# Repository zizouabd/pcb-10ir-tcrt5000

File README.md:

# Module de Capteurs Suiveur de Ligne (10x TCRT5000)

Ce projet contient les fichiers de conception pour un module PCB incurvé conçu pour le suivi de ligne, intégrant 10 capteurs infrarouges TCRT5000.

## Schéma Électrique
Le circuit est composé de 10 capteurs optiques (U1 à U10), chacun accompagné d'une résistance de 220 ohms pour la LED émettrice et d'une résistance de pull-up de 10k ohms pour le phototransistor récepteur[cite: 1]. Les signaux (SIG_S1 à SIG_S10) sont regroupés sur un connecteur central à 12 broches avec l'alimentation (VCC) et la masse (GND).

## Routage du PCB
Le routage a été optimisé sur un circuit imprimé de forme incurvée pour s'adapter à l'avant d'un robot, avec deux trous de montage (H1 et H2).

## Vues 3D

### Face Supérieure (Composants)
La face supérieure accueille l'ensemble des résistances traversantes, le condensateur de découplage, et le connecteur principal J1.

### Face Inférieure (Capteurs)
La face inférieure est dédiée exclusivement aux 10 capteurs infrarouges TCRT5000 orientés vers le sol pour la détection de ligne.

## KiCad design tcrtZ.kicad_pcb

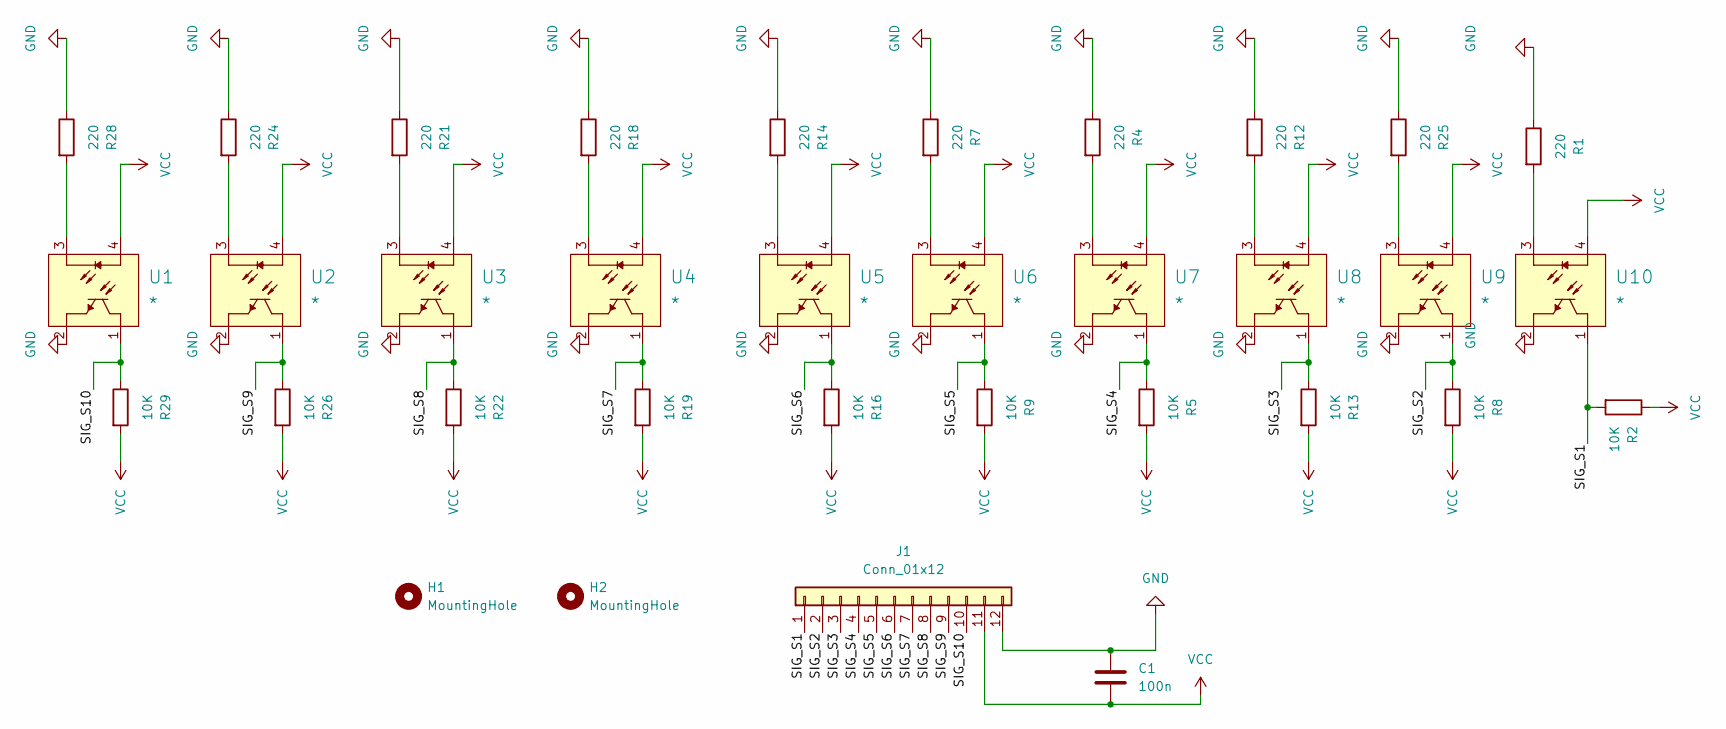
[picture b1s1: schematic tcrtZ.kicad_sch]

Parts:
C1: 100n; C_0805_2012Metric_Pad1.18x1.45mm_HandSolder
H1, H2: MountingHole; MountingHole_3.2mm_M3
J1: Conn_01x12; PinHeader_1x12_P2.54mm_Vertical
R1, R4, R7, R12, R14, R18, R21, R24, R25, R28: 220; R_Axial_DIN0207_L6.3mm_D2.5mm_P10.16mm_Horizontal
R2, R5, R8, R9, R13, R16, R19, R22, R26, R29: 10K; R_Axial_DIN0207_L6.3mm_D2.5mm_P10.16mm_Horizontal
U1, U2, U3, U4, U5, U6, U7, U8, U9, U10: *; Vishay_TCRT5000

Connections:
/SIG_S1: J1.1, R2.2, U10.1 (CO)
/SIG_S2: J1.2, R8.1, U9.1 (CO)
/SIG_S3: J1.3, R13.1, U8.1 (CO)
/SIG_S4: J1.4, R5.1, U7.1 (CO)
/SIG_S5: J1.5, R9.1, U6.1 (CO)
/SIG_S6: J1.6, R16.1, U5.1 (CO)
/SIG_S7: J1.7, R19.1, U4.1 (CO)
/SIG_S8: J1.8, R22.1, U3.1 (CO)
/SIG_S9: J1.9, R26.1, U2.1 (CO)
/SIG_S10: J1.10, R29.1, U1.1 (CO)
GND: C1.1, J1.12, R1.1, R4.1, R7.1, R12.1, R14.1, R18.1, R21.1, R24.1, R25.1, R28.1, U1.2 (E), U2.2 (E), U3.2 (E), U4.2 (E), U5.2 (E), U6.2 (E), U7.2 (E), U8.2 (E), U9.2 (E), U10.2 (E)
unnamed: R28.2, U1.3 (C)
unnamed: R24.2, U2.3 (C)
unnamed: R21.2, U3.3 (C)
unnamed: R18.2, U4.3 (C)
unnamed: R14.2, U5.3 (C)
unnamed: R7.2, U6.3 (C)
unnamed: R4.2, U7.3 (C)
unnamed: R12.2, U8.3 (C)
unnamed: R25.2, U9.3 (C)
unnamed: R1.2, U10.3 (C)
VCC: C1.2, J1.11, R2.1, R5.2, R8.2, R9.2, R13.2, R16.2, R19.2, R22.2, R26.2, R29.2, U1.4 (A), U2.4 (A), U3.4 (A), U4.4 (A), U5.4 (A), U6.4 (A), U7.4 (A), U8.4 (A), U9.4 (A), U10.4 (A)

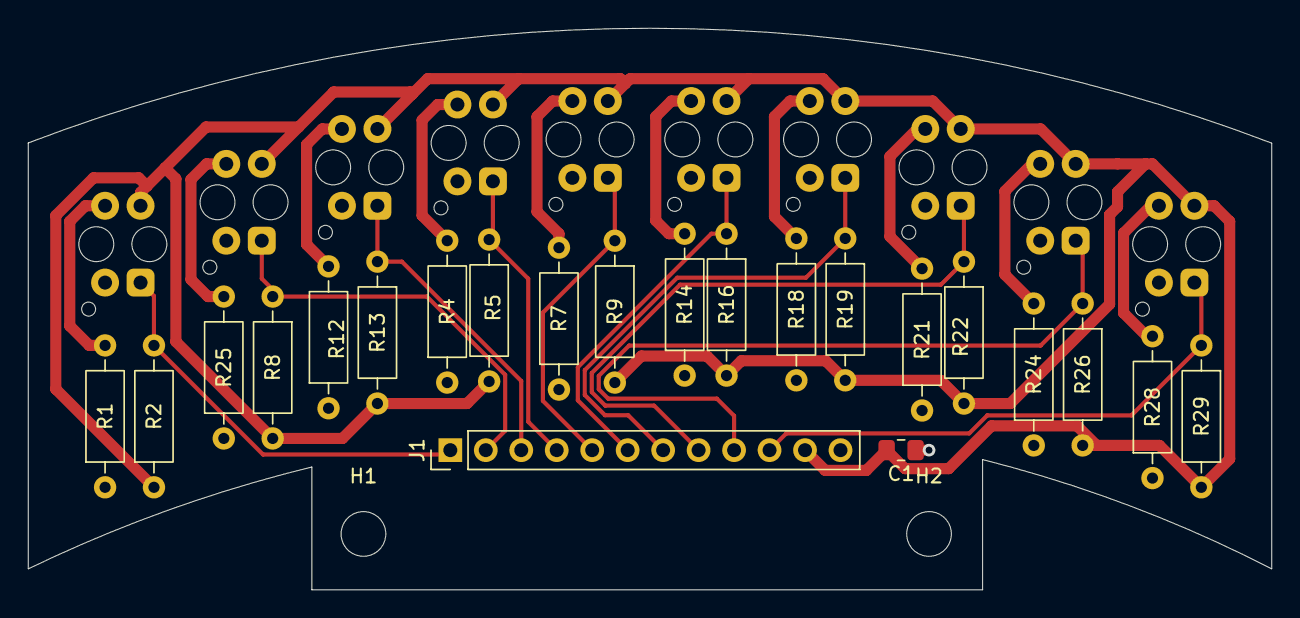
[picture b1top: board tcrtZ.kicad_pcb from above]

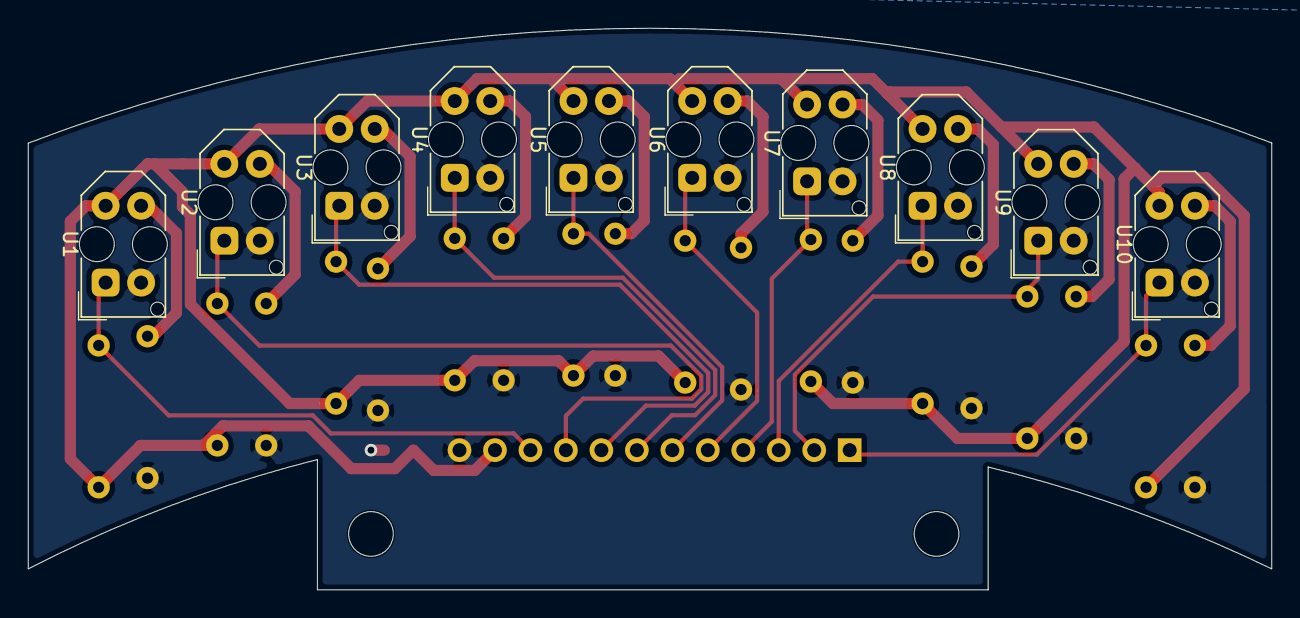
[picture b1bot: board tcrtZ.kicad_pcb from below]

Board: 2 copper layers, 89.0 x 40.2 mm, 34 parts (10 on the bottom side), 22 nets.
